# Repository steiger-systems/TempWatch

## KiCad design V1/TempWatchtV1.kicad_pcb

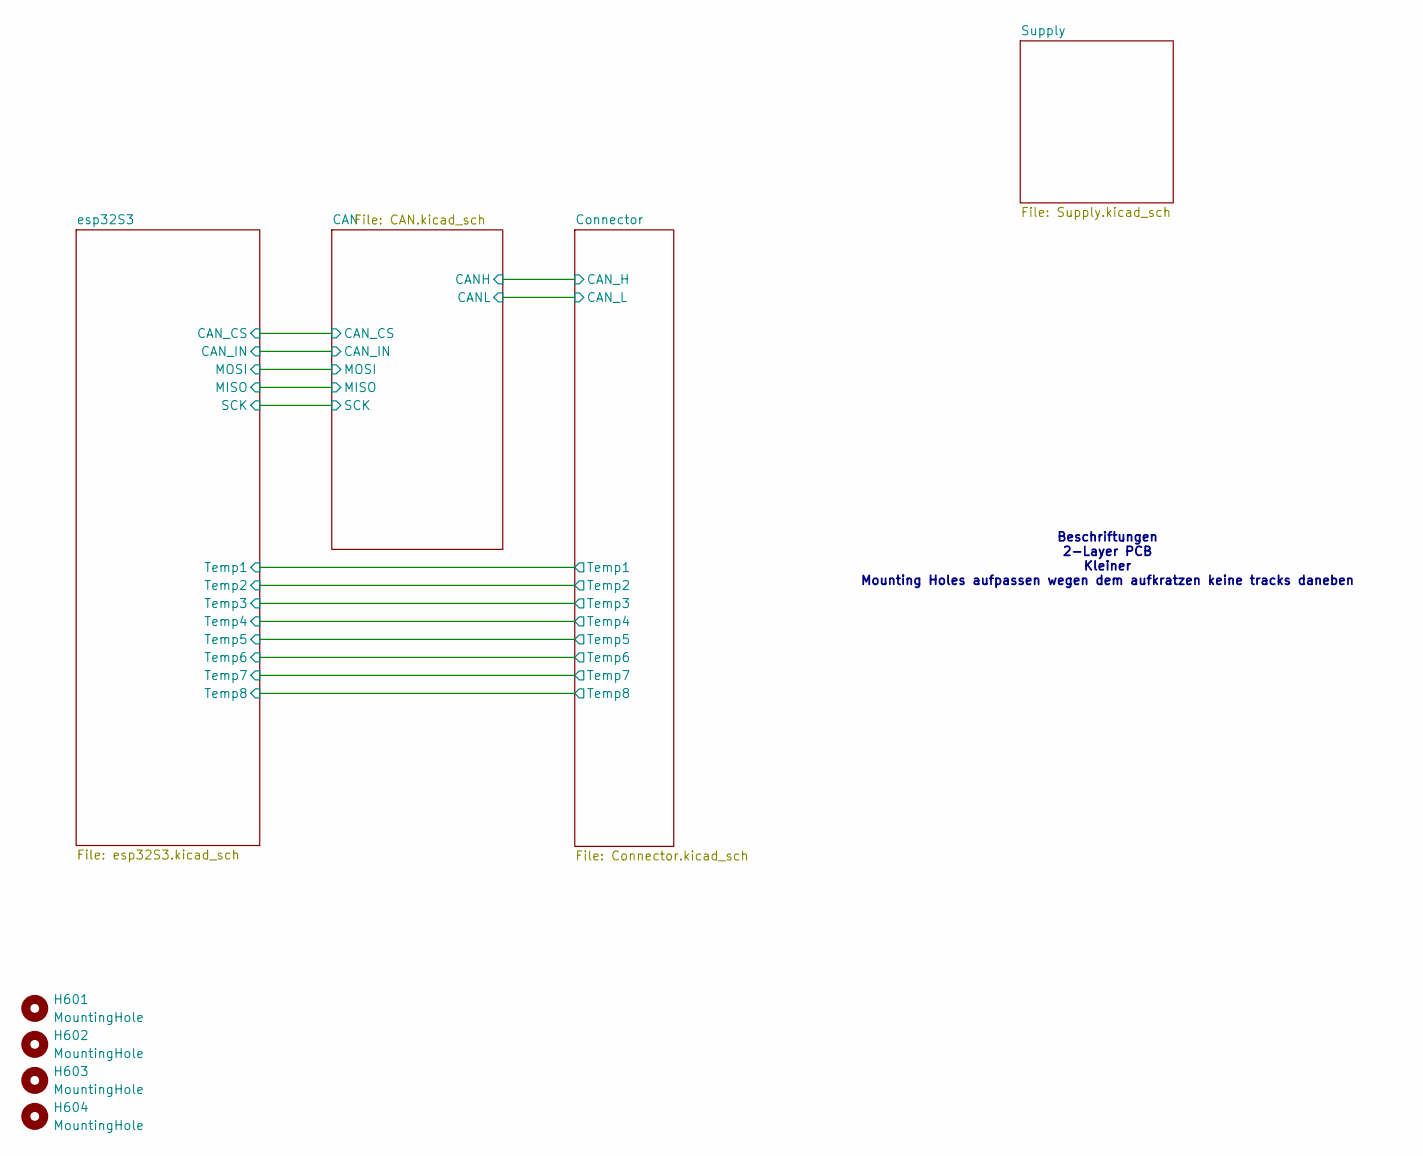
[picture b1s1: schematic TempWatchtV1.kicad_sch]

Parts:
H601, H602, H603, H604: MountingHole; MountingHole_3.2mm_M3_DIN965

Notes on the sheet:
Beschriftungen 2-Layer PCB Kleiner Mounting Holes aufpassen wegen dem aufkratzen keine tracks daneben

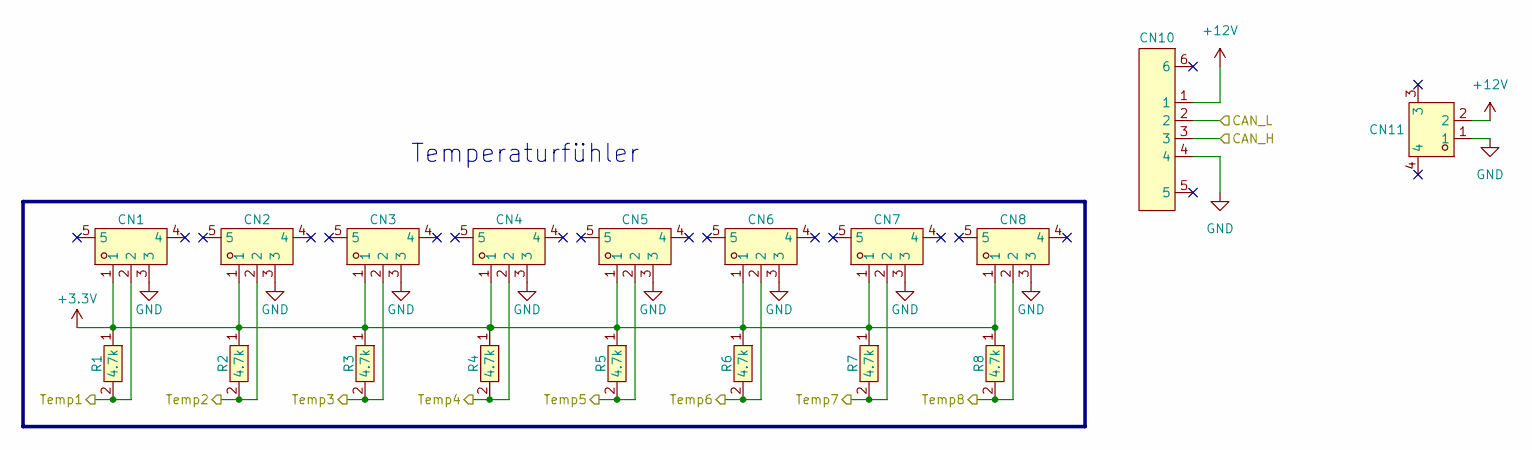
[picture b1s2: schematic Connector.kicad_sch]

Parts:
CN1, CN2, CN3, CN4, CN5, CN6, CN7, CN8: SM03B-SRSS-TB(LF)(SN)(P); CONN-SMD_SM03B-SRSS-TB-LF-SN-P; LCSC Part C160403
CN10: SM04B-SRSS-TB (LF)(SN); CONN-SMD_4P-P1.00_SM04B-SRSS-TB-LF-SN; LCSC Part C160404
CN11: SM02B-PASS-1-TBT(LF)(SN); CONN-SMD_SM02B-PASS-1-TBT-LF-SN; LCSC Part C265416
R1, R2, R3, R4, R5, R6, R7, R8: 4.7k; R0603; LCSC Part C2907034

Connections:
+3.3V: CN1.1, CN2.1, CN3.1, CN4.1, CN5.1, CN6.1, CN7.1, CN8.1, R1.1, R2.1, R3.1, R4.1, R5.1, R6.1, R7.1, R8.1; also elsewhere on the board
+12V: CN10.1, CN11.2; also elsewhere on the board
/CAN/CANH: CN10.3; also elsewhere on the board
/CAN/CANL: CN10.2; also elsewhere on the board
/Connector/Temp1: CN1.2, R1.2; also elsewhere on the board
/Connector/Temp2: CN2.2, R2.2; also elsewhere on the board
/Connector/Temp3: CN3.2, R3.2; also elsewhere on the board
/Connector/Temp4: CN4.2, R4.2; also elsewhere on the board
/Connector/Temp5: CN5.2, R5.2; also elsewhere on the board
/Connector/Temp6: CN6.2, R6.2; also elsewhere on the board
/Connector/Temp7: CN7.2, R7.2; also elsewhere on the board
/Connector/Temp8: CN8.2, R8.2; also elsewhere on the board
GND: CN1.3, CN2.3, CN3.3, CN4.3, CN5.3, CN6.3, CN7.3, CN8.3, CN10.4, CN11.1; also elsewhere on the board

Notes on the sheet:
Temperaturfühler

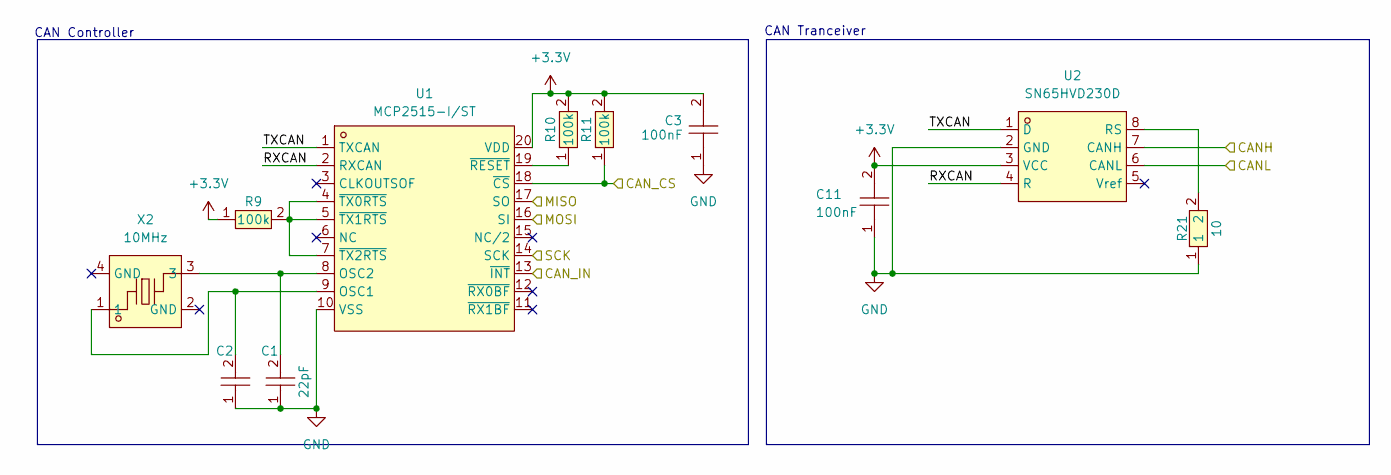
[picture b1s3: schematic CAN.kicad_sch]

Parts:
C1, C2: 22pF; C0603; LCSC Part C105620
C3, C11: 100nF; C0603; LCSC Part C14663
R9, R10, R11: 100k; R0402; LCSC Part C481918
R21: 10; R0603; LCSC Part C403411
U1: MCP2515-I/ST; TSSOP-20_L6.5-W4.4-P0.65-LS6.4-BL; LCSC Part C15193
U2: SN65HVD230D; SOIC-8_L4.9-W3.9-P1.27-LS6.0-BL; LCSC Part C1543812
X2: 10MHz; CRYSTAL-SMD_4P-L3.2-W2.5-BL; LCSC Part C20885034

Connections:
+3.3V: C3.2, C11.2, R9.1, R10.2, R11.2, U1.20 (VDD), U2.3 (VCC); also elsewhere on the board
/CAN/CANH: U2.7 (CANH); also elsewhere on the board
/CAN/CANL: U2.6 (CANL); also elsewhere on the board
/CAN/CAN_CS: R11.1, U1.18 (~CS); also elsewhere on the board
/CAN/CAN_IN: U1.13 (~INT); also elsewhere on the board
/CAN/MISO: U1.17 (SO); also elsewhere on the board
/CAN/MOSI: U1.16 (SI); also elsewhere on the board
/CAN/RXCAN: U1.2 (RXCAN), U2.4 (R)
/CAN/SCK: U1.14 (SCK); also elsewhere on the board
/CAN/TXCAN: U1.1 (TXCAN), U2.1 (D)
GND: C1.1, C2.1, C3.1, C11.1, R21.1, U1.10 (VSS), U2.2 (GND); also elsewhere on the board
unnamed: C2.2, U1.9 (OSC1), X2.1
unnamed: C1.2, U1.8 (OSC2), X2.3
unnamed: R10.1, U1.19 (~RESET)
unnamed: R9.2, U1.4 (~TX0RTS), U1.5 (~TX1RTS), U1.7 (~TX2RTS)
unnamed: R21.2, U2.8 (RS)

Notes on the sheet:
CAN Tranceiver
CAN Controller

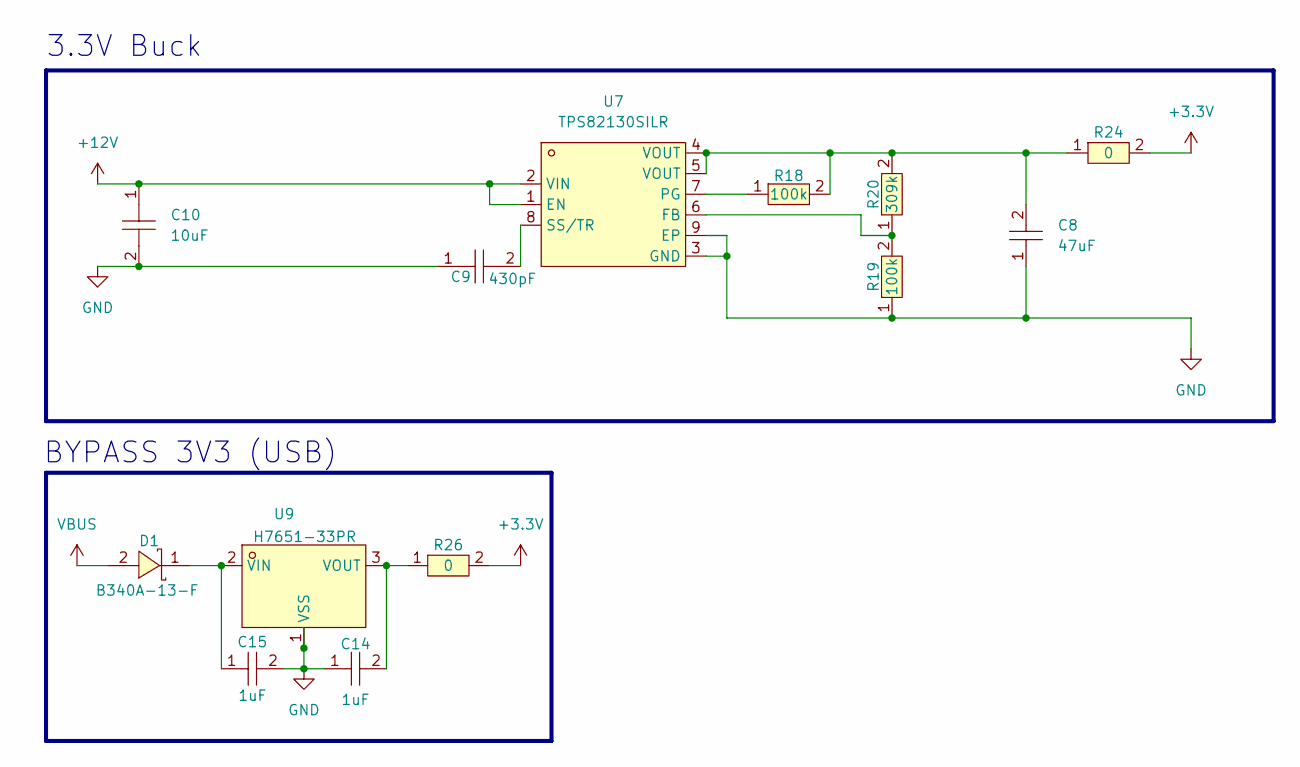
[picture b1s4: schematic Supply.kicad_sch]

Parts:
C8: 47uF; C0603; LCSC Part C140782
C9: 430pF; C0402; LCSC Part C2193561
C10: 10uF; C1206; LCSC Part C89632
C14, C15: 1uF; C0805; LCSC Part C28323
D1: B340A-13-F; SMA_L4.4-W2.6-LS5.0-RD; LCSC Part C85098
R18, R19: 100k; R0402; LCSC Part C481918
R20: 309k; R0402; LCSC Part C5713270
R24, R26: 0; R1206; LCSC Part C2907406
U7: TPS82130SILR; USIP-8_L3.0-W2.8-P0.65-TL-EP; LCSC Part C473914
U9: H7651-33PR; SOT-89-3_L4.5-W2.5-P1.50-LS4.1-BR; LCSC Part C411050

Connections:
+3.3V: R24.2, R26.2; also elsewhere on the board
+12V: C10.1, U7.1 (EN), U7.2 (VIN); also elsewhere on the board
GND: C8.1, C9.1, C10.2, C14.1, C15.2, R19.1, U7.3 (GND), U7.9 (EP), U9.1 (VSS); also elsewhere on the board
unnamed: C8.2, R18.2, R20.2, R24.1, U7.4 (VOUT), U7.5 (VOUT)
unnamed: C15.1, D1.1 (K), U9.2 (VIN)
unnamed: R19.2, R20.1, U7.6 (FB)
unnamed: R18.1, U7.7 (PG)
unnamed: C9.2, U7.8 (SS/TR)
unnamed: C14.2, R26.1, U9.3 (VOUT)
VBUS: D1.2 (A); also elsewhere on the board

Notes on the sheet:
BYPASS 3V3 (USB)
3.3V Buck

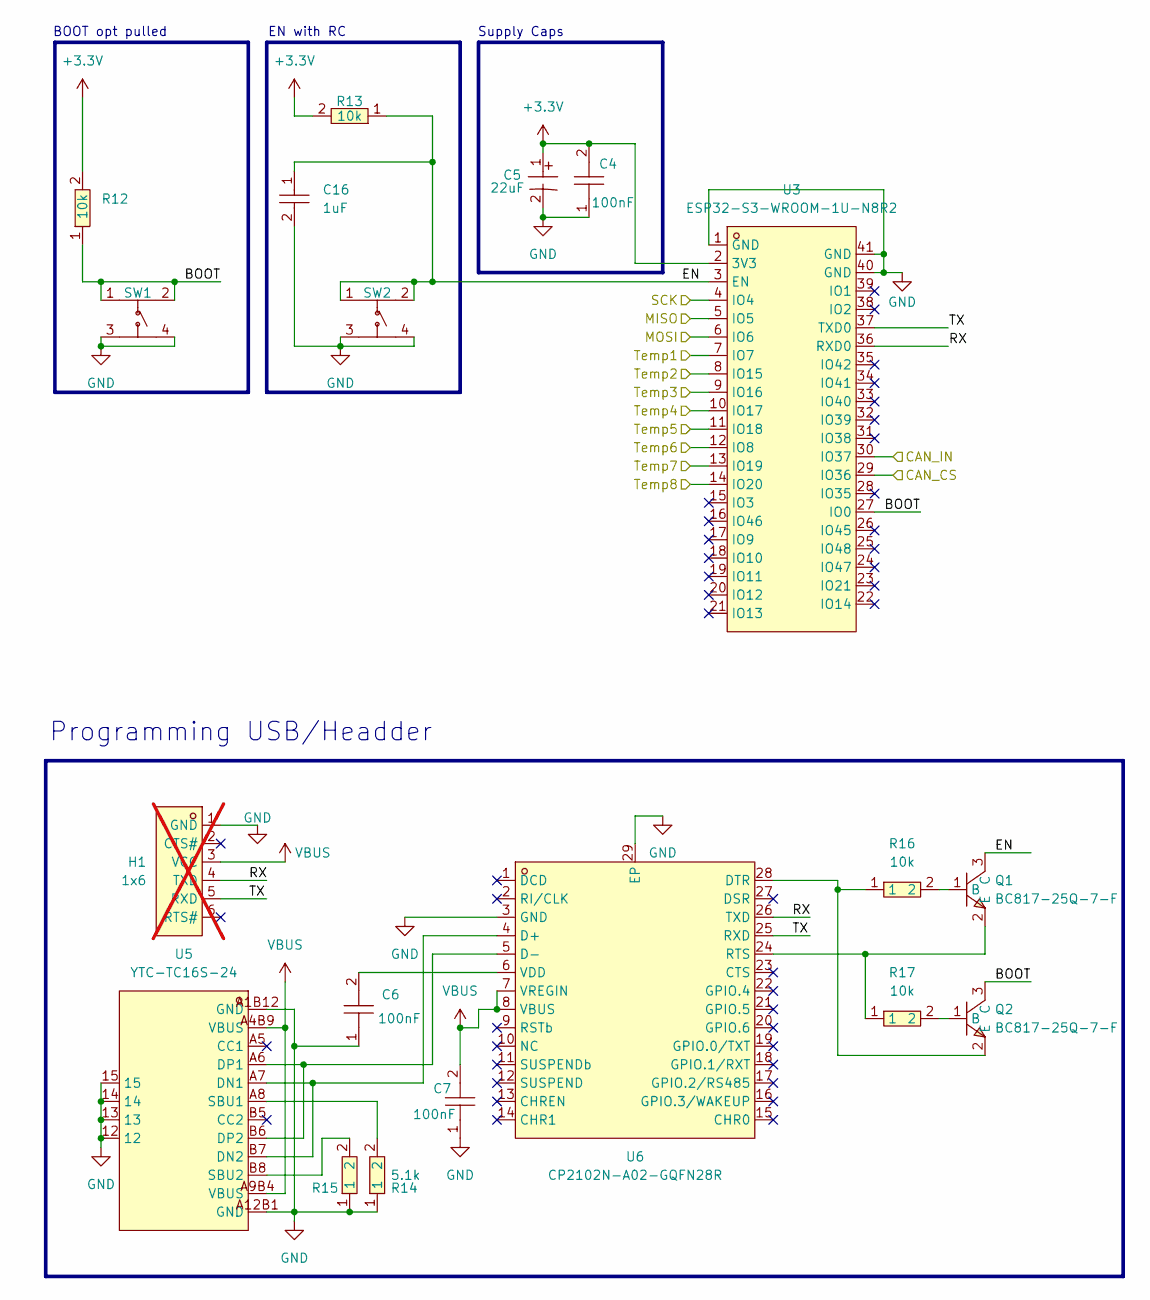
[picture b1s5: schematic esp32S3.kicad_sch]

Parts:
C4, C6, C7: 100nF; C0603; LCSC Part C14663
C5: 22uF; CAP-SMD_BD4.0-L4.3-W4.3-LS5.1-FD; LCSC Part C131114
C16: 1uF; C0805; LCSC Part C28323
H1: 1x6; HDR-TH_6P-P2.54-V-M-1; LCSC Part C42431796; not fitted
Q1, Q2: BC817-25Q-7-F; SOT-23-3_L2.9-W1.3-P1.90-LS2.4-BR; LCSC Part C559579
R12, R13, R16, R17: 10k; R0603; LCSC Part C98220
R14, R15: 5.1k; R0603; LCSC Part C186203
SW1, SW2: KH-6X6X5H-STM; SW-SMD_4P-L6.0-W6.0-P4.50-LS9.0_H5.0; LCSC Part C2837531
U3: ESP32-S3-WROOM-1U-N8R2; WIRELM-SMD_ESP32-S3-WROOM-1U; LCSC Part C3013944
U5: YTC-TC16S-24; USB-C-SMD_YTC-TC16S-24; LCSC Part C2927291
U6: CP2102N-A02-GQFN28R; QFN-28_L5.0-W5.0-P0.50-TL-EP3.3; LCSC Part C964632

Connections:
+3.3V: C4.2, C5.1, R12.2, R13.2, U3.2 (3V3); also elsewhere on the board
/CAN/CAN_CS: U3.29 (IO36); also elsewhere on the board
/CAN/CAN_IN: U3.30 (IO37); also elsewhere on the board
/CAN/MISO: U3.5 (IO5); also elsewhere on the board
/CAN/MOSI: U3.6 (IO6); also elsewhere on the board
/CAN/SCK: U3.4 (IO4); also elsewhere on the board
/Connector/Temp1: U3.7 (IO7); also elsewhere on the board
/Connector/Temp2: U3.8 (IO15); also elsewhere on the board
/Connector/Temp3: U3.9 (IO16); also elsewhere on the board
/Connector/Temp4: U3.10 (IO17); also elsewhere on the board
/Connector/Temp5: U3.11 (IO18); also elsewhere on the board
/Connector/Temp6: U3.12 (IO8); also elsewhere on the board
/Connector/Temp7: U3.13 (IO19); also elsewhere on the board
/Connector/Temp8: U3.14 (IO20); also elsewhere on the board
/esp32S3/BOOT: Q2.3 (C), R12.1, SW1.1, SW1.2, U3.27 (IO0)
/esp32S3/EN: C16.1, Q1.3 (C), R13.1, SW2.1, SW2.2, U3.3 (EN)
/esp32S3/RX: H1.4 (TXD), U3.36 (RXD0), U6.26 (TXD)
/esp32S3/TX: H1.5 (RXD), U3.37 (TXD0), U6.25 (RXD)
GND: C4.1, C5.2, C6.1, C7.1, C16.2, H1.1 (GND), R14.1, R15.1, SW1.3, SW1.4, SW2.3, SW2.4, U3.1 (GND), U3.40 (GND), U3.41 (GND), U5.12, U5.13, U5.14, U5.15, U5.A1B12 (GND), U5.A12B1 (GND), U6.3 (GND), U6.29 (EP); also elsewhere on the board
unnamed: Q1.1 (B), R16.2
unnamed: Q1.2 (E), R17.1, U6.24 (RTS)
unnamed: Q2.1 (B), R17.2
unnamed: Q2.2 (E), R16.1, U6.28 (DTR)
unnamed: U5.A7 (DN1), U5.B7 (DN2), U6.4 (D+)
unnamed: U5.A6 (DP1), U5.B6 (DP2), U6.5 (D-)
unnamed: R14.2, U5.A8 (SBU1)
unnamed: R15.2, U5.B8 (SBU2)
unnamed: C6.2, U6.6 (VDD)
VBUS: C7.2, H1.3 (VCC), U5.A4B9 (VBUS), U5.A9B4 (VBUS), U6.7 (VREGIN), U6.8 (VBUS); also elsewhere on the board

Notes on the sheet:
Supply Caps
EN with RC
BOOT opt pulled
Programming USB/Headder

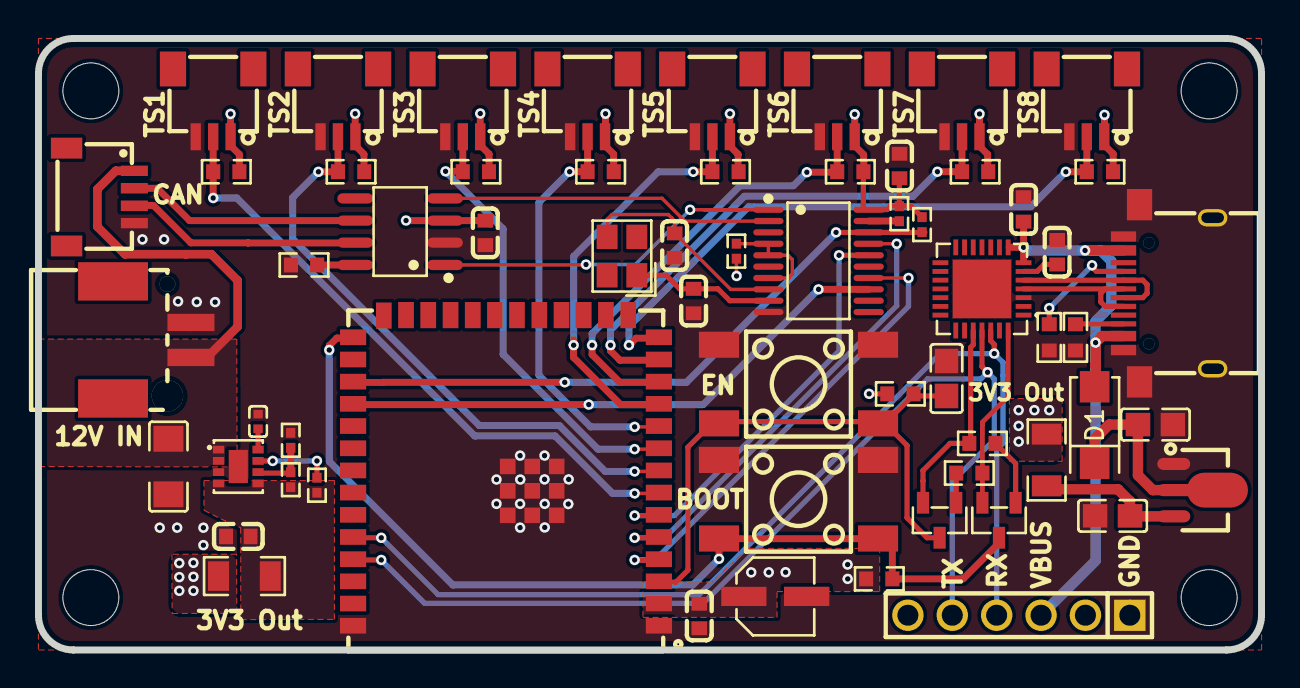
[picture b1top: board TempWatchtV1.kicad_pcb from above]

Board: 4 copper layers, 70.0 x 35.0 mm, 65 parts (0 on the bottom side), 45 nets.

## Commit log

2026-01-14 Latest
